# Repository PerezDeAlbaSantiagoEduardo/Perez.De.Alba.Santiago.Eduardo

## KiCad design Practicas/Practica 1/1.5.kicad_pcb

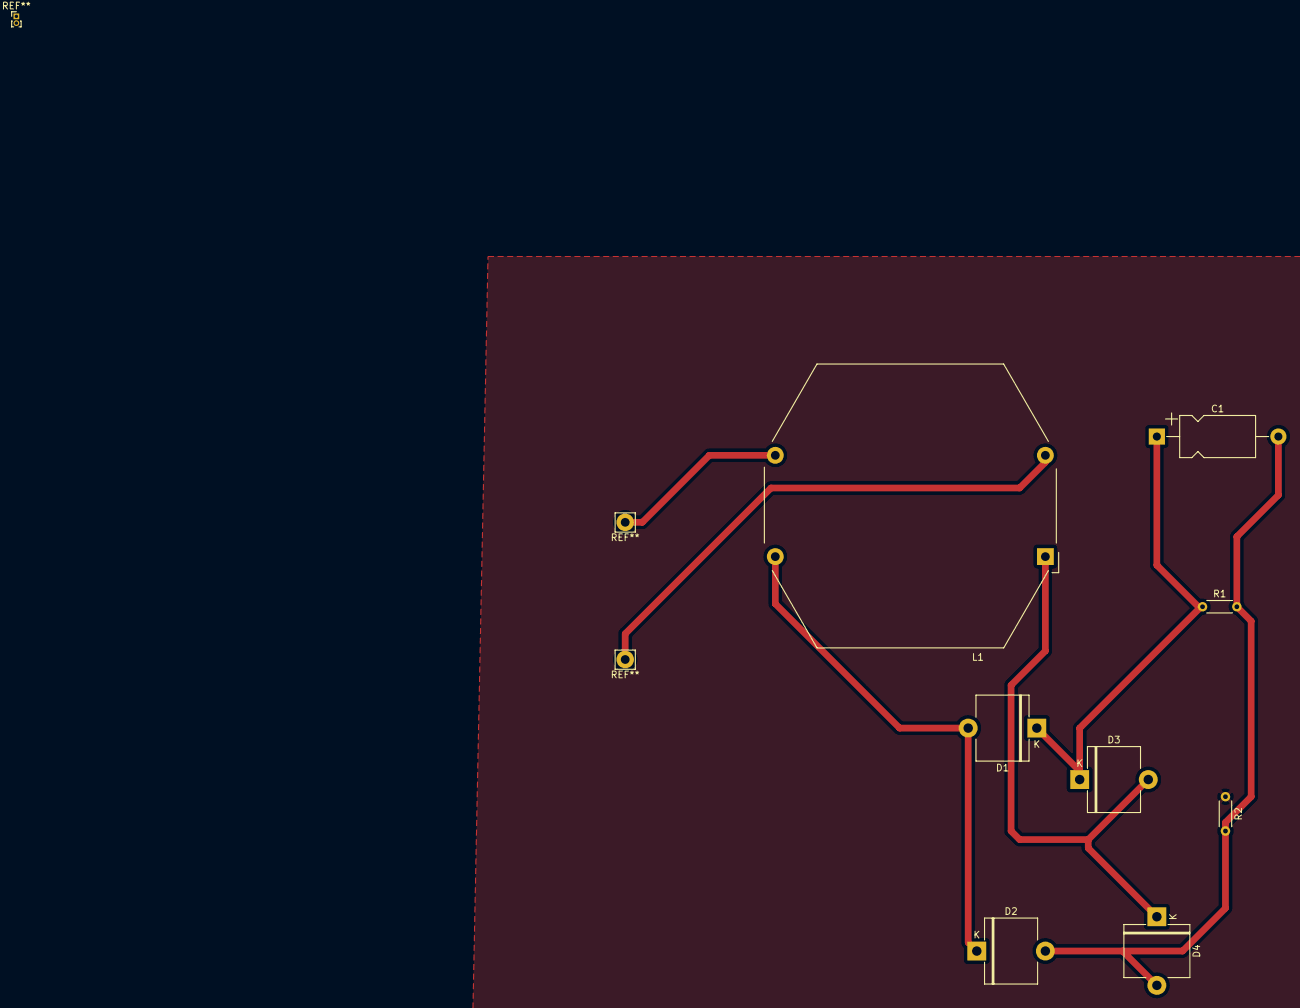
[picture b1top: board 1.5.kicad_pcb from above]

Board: 2 copper layers, 8 parts (0 on the bottom side), 4 nets.

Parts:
C1: C; CP_Axial_L11.0mm_D6.0mm_P18.00mm_Horizontal
D1, D2, D3, D4: D; D_5KP_P10.16mm_Horizontal
L1: L; Choke_Schaffner_RN152-04-43.0x41.8mm
R1, R2: R; R_Axial_DIN0204_L3.6mm_D1.6mm_P5.08mm_Horizontal

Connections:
unnamed: C1.1, D1.1, D3.1, R1.1
unnamed: C1.2, D2.2, D4.2, R1.2, R2.2
unnamed: D1.2, D2.1, L1.2
VAC: D3.2, D4.1, L1.1

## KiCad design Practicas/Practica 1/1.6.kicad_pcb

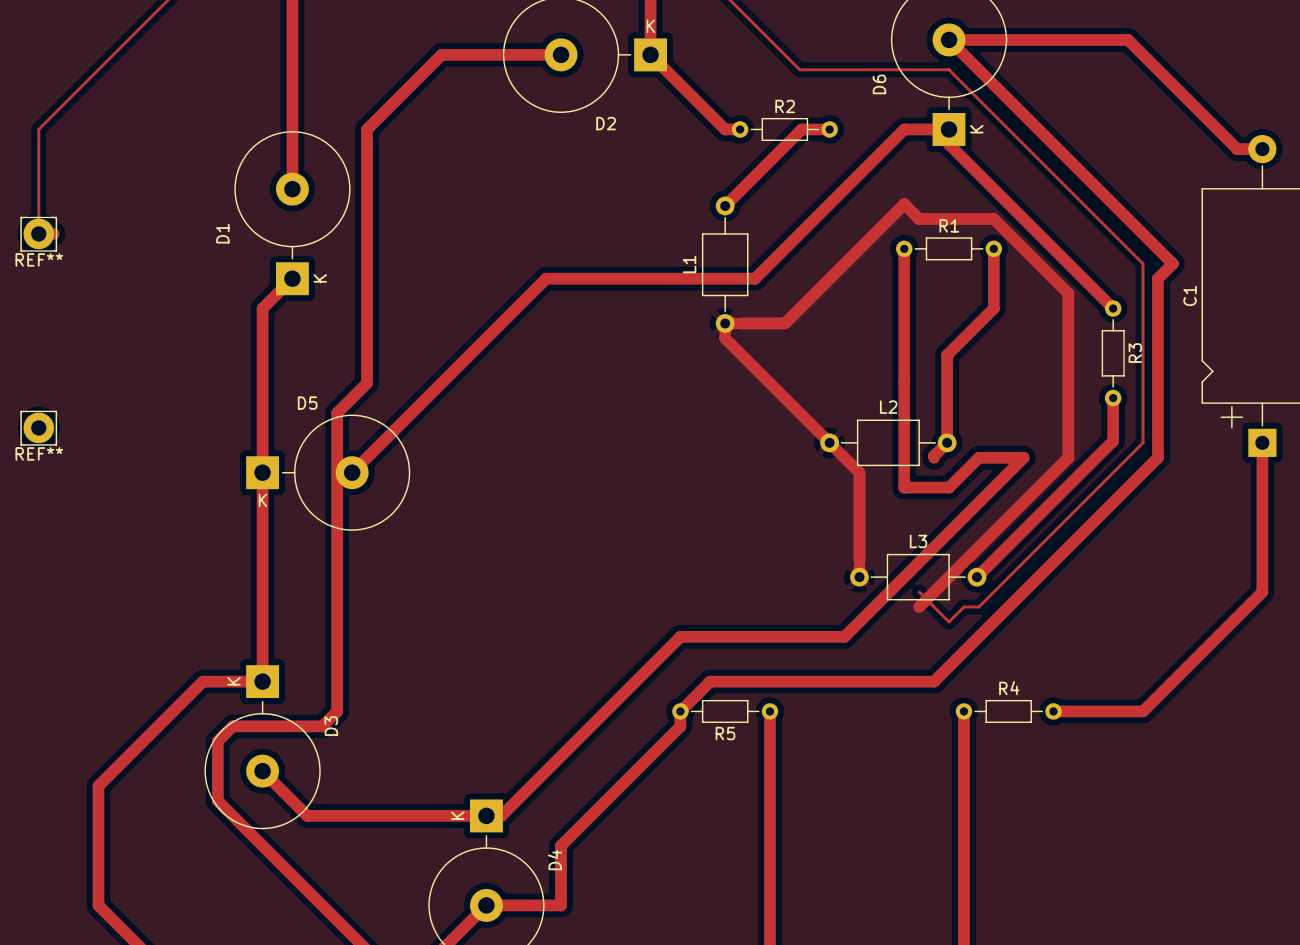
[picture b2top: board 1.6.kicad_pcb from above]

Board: 2 copper layers, 15 parts (0 on the bottom side), 10 nets.

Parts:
C1: C; CP_Axial_L18.0mm_D10.0mm_P25.00mm_Horizontal
D1, D2, D3, D4, D5, D6: D; D_5KP_P7.62mm_Vertical_KathodeUp
L1, L2, L3: L; L_Axial_L5.0mm_D3.6mm_P10.00mm_Horizontal_Murata_BL01RN1A2A2
R1, R2, R3, R4, R5: R; R_Axial_DIN0204_L3.6mm_D1.6mm_P7.62mm_Horizontal

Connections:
unnamed: C1.1, R4.2
unnamed: C1.2, D2.2, D4.2, D6.2, R5.2
unnamed: D1.1, D3.1, D5.1, R4.1, R5.1
unnamed: D1.2, D2.1, R2.1
unnamed: D3.2, D4.1, R1.1
unnamed: D5.2, D6.1, R3.1
unnamed: L1.2, R2.2
unnamed: L2.2, R1.2
unnamed: L3.2, R3.2
VAC: L1.1, L2.1, L3.1

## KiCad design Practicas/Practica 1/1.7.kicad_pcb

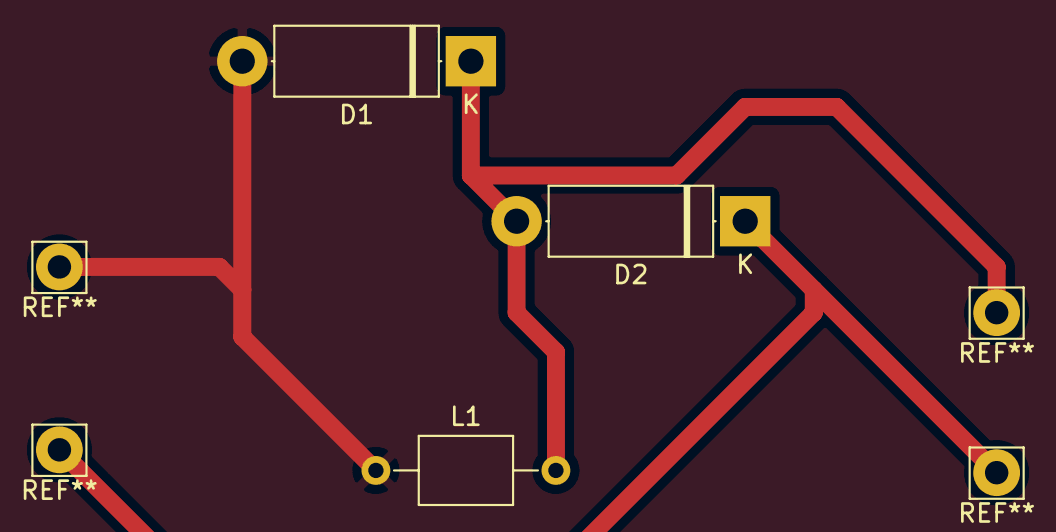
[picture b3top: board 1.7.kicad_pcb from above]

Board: 2 copper layers, 3 parts (0 on the bottom side), 2 nets.

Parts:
D1, D2: D; D_5W_P12.70mm_Horizontal
L1: L; L_Axial_L5.0mm_D3.6mm_P10.00mm_Horizontal_Murata_BL01RN1A2A2

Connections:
GNDREF: D1.2, L1.1
unnamed: D1.1, D2.2, L1.2

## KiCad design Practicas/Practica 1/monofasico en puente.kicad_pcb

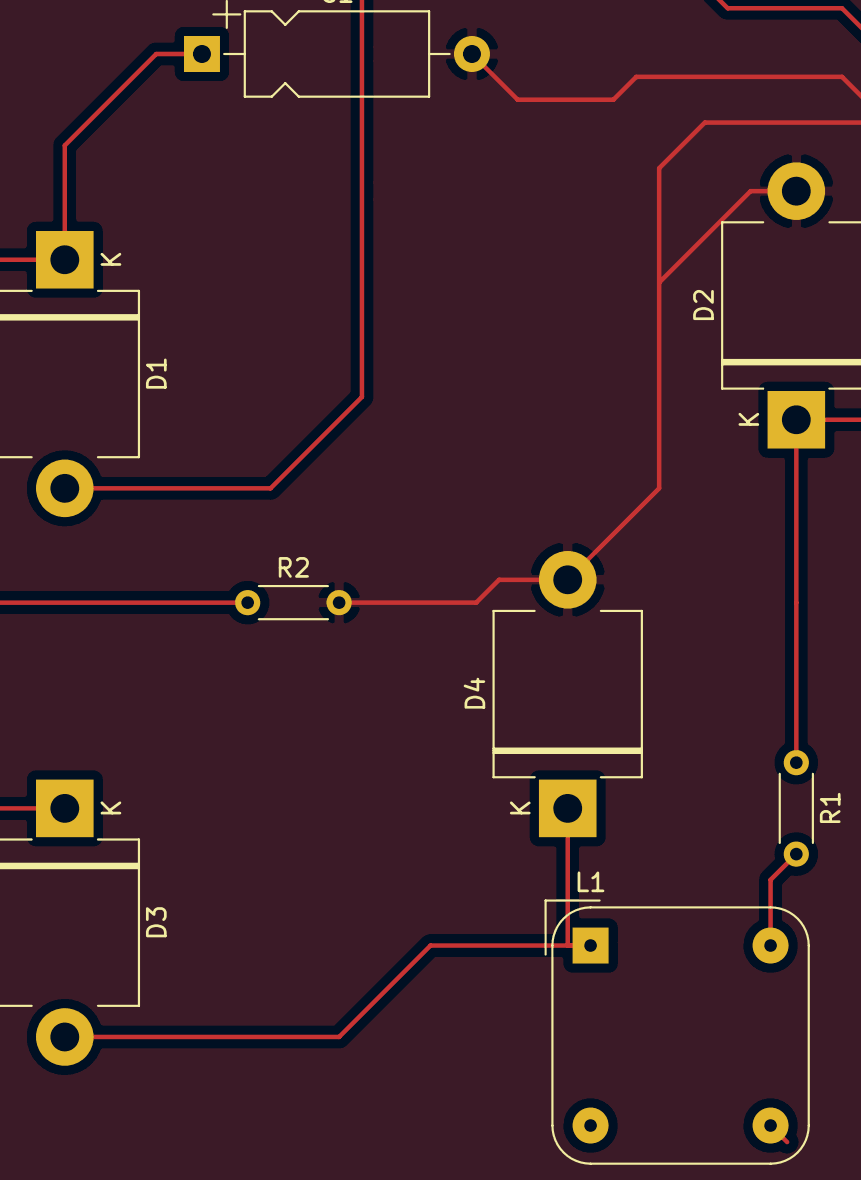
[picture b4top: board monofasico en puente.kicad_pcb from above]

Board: 2 copper layers, 8 parts (0 on the bottom side), 5 nets.

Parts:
C1: 1mf; CP_Axial_L10.0mm_D4.5mm_P15.00mm_Horizontal
D1, D2, D3, D4: D; D_5KPW_P12.70mm_Horizontal
L1: 1mh; Choke_Schaffner_RN102-04-14.0x14.0mm
R1, R2: 10; R_Axial_DIN0204_L3.6mm_D1.6mm_P5.08mm_Horizontal

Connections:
AC: D3.2, D4.1, L1.1
GNDREF: C1.2, D2.2, D4.2, R2.2
unnamed: C1.1, D1.1, D3.1, R2.1
unnamed: D1.2, D2.1, R1.1
unnamed: L1.2, R1.2

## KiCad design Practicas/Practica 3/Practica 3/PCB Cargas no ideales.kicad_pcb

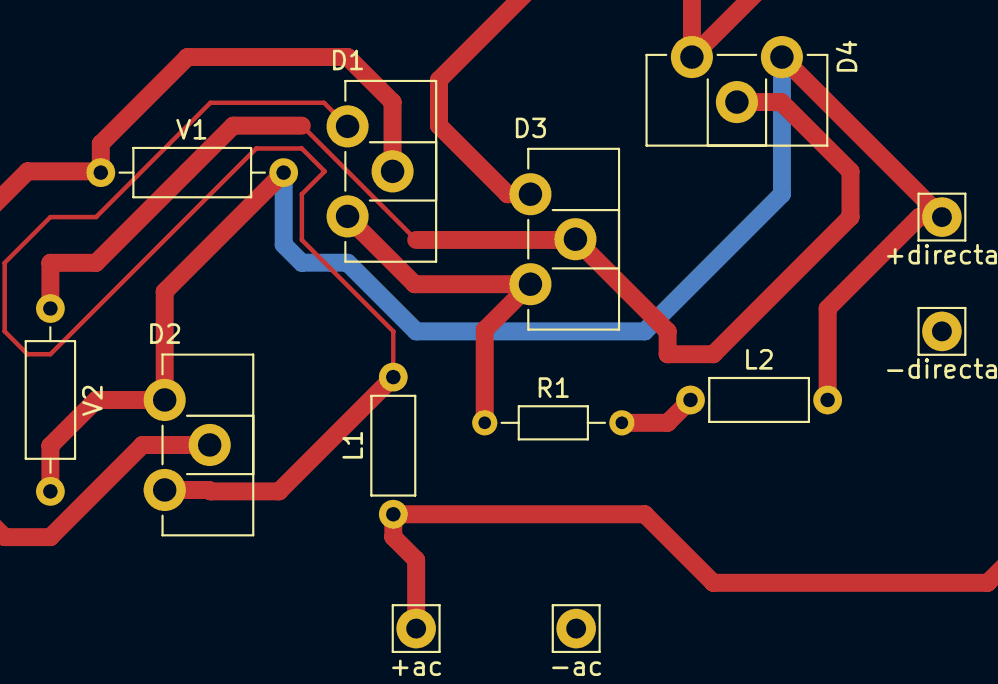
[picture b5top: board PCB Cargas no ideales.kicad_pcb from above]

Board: 2 copper layers, 13 parts (0 on the bottom side), 7 nets.

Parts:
+ac: Pin_D1.1mm_L8.5mm_W2.5mm_FlatFork
+directa: Pin_D1.1mm_L8.5mm_W2.5mm_FlatFork
-ac: Pin_D1.1mm_L8.5mm_W2.5mm_FlatFork
-directa: Pin_D1.1mm_L8.5mm_W2.5mm_FlatFork
D1, D2, D3, D4: Q_SCR_AGK; Potentiometer_ACP_CA9-H2,5_Horizontal
L1, L2: L; L_Axial_L5.3mm_D2.2mm_P7.62mm_Horizontal_Vishay_IM-1
R1: R; R_Axial_DIN0204_L3.6mm_D1.6mm_P7.62mm_Horizontal
V1, V2: VPULSE; R_Axial_DIN0207_L6.3mm_D2.5mm_P10.16mm_Horizontal

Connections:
AC: D3.1, D4.3, L1.1
Earth: D2.1, D4.1, L2.2, V1.2, V2.2
unnamed: D1.1, D2.3, L1.2
unnamed: D1.2, D2.2, V1.1
unnamed: D1.3, D3.3, R1.1
unnamed: D3.2, D4.2, V2.1
unnamed: L2.1, R1.2
